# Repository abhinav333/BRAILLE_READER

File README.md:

# Braille e-book reader

Refer work *A. Kulkarni and K. Bhurchandi, "Low Cost E-Book Reading Device for Blind People," 2015 International Conference on Computing Communication Control and Automation, 2015, pp. 516-520, doi: 10.1109/ICCUBEA.2015.106.*

Program, schematics and images<br />
File description:<br />
**braillecode.c** - Lookup table for mapping of aplhanumeric characters to respective braille characters<br />
**buzzer.c** - Contains modules to generate variety of buzzer notifications<br />
**lcd.c** - Consists of lcd display functions. Used only in test mode.<br />
**main.c** - Main program<br />
**mmc.c** - PetitFATFS library: MMC Disk image control modules<br />
**pff.c** - PetitFATFS library: High level SD Card control modules<br />
**pffconf.h** - PetitFATFS library: Version and configuration file<br />
**spi.h** - Low level SPI access functions<br />
**Schematics** - Eagle PCB design files<br />
**test cell** - Contains debug modules for each braille cell<br />
**Hardware** - Device images<br />

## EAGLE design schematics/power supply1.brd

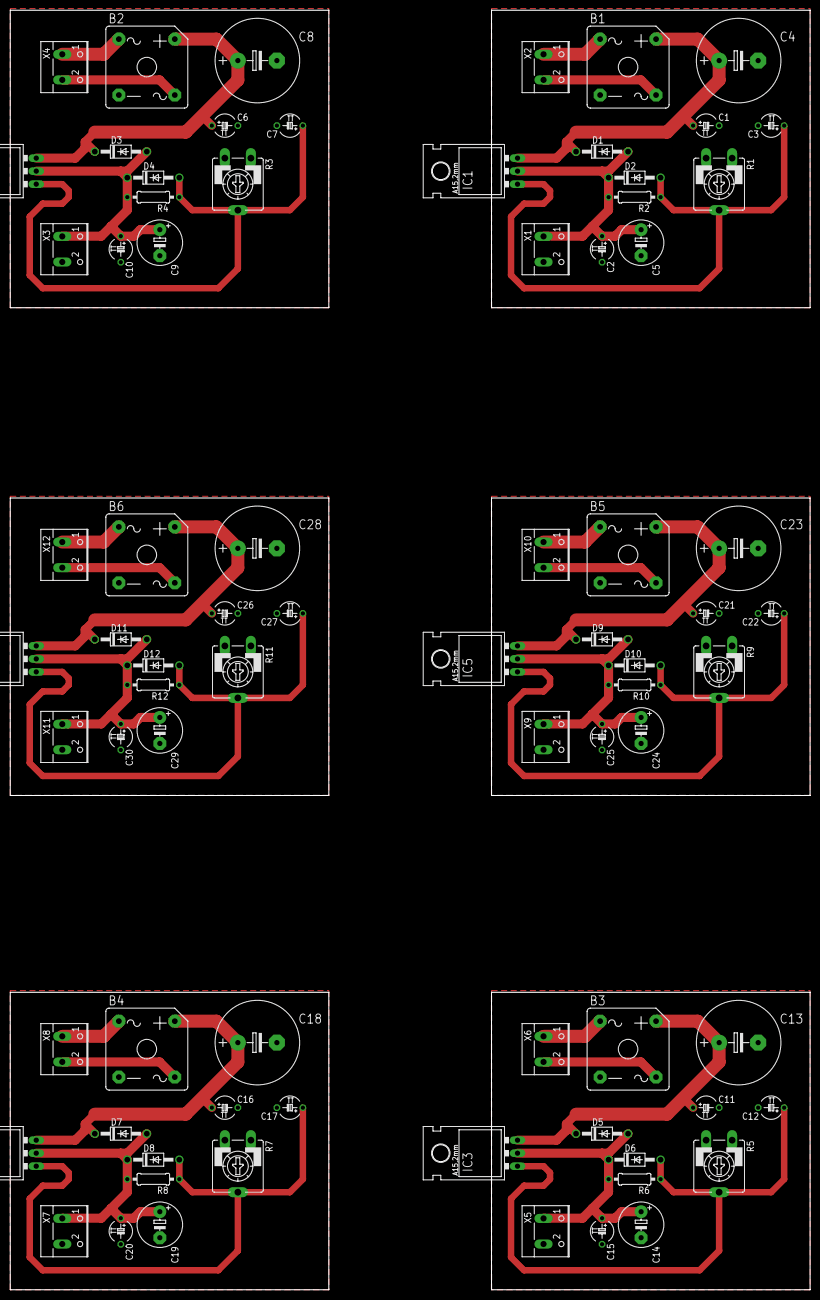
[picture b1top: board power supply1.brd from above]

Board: 2 copper layers, 156.2 x 249.9 mm, 78 parts (0 on the bottom side), 36 nets.

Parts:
B1, B2, B3, B4, B5, B6: GBPC1
C1, C2, C3, C6, C7, C10, C11, C12, C15, C16, C17, C20, C21, C22, C25, C26, C27, C30: 0.1uF; TAP5-45
C4, C8, C13, C18, C23, C28: E7,5-16
C5, C9, C14, C19, C24, C29: E5-8,5
D1, D2, D3, D4, D5, D6, D7, D8, D9, D10, D11, D12: 1N4004; DO41-10
IC1, IC2, IC3, IC4, IC5, IC6: LM317MBT; TO220L1
R1, R3, R5, R7, R9, R11: CA9V
R2, R4, R6, R8, R10, R12: 120R; 0207/10
X1, X2, X3, X4, X5, X6, X7, X8, X9, X10, X11, X12: W237-102

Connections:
AGND: B1.-, C1.-, C2.-, C3.-, C4.-, C5.-, R1.A, X1.2
AGND1: B2.-, C6.-, C7.-, C8.-, C9.-, C10.-, R3.A, X3.2
AGND2: B3.-, C11.-, C12.-, C13.-, C14.-, C15.-, R5.A, X5.2
AGND3: B4.-, C16.-, C17.-, C18.-, C19.-, C20.-, R7.A, X7.2
AGND4: B5.-, C21.-, C22.-, C23.-, C24.-, C25.-, R9.A, X9.2
AGND5: B6.-, C26.-, C27.-, C28.-, C29.-, C30.-, R11.A, X11.2
unnamed: B1.+, C1.+, C4.+, D1.C, IC1.3
unnamed: C2.+, C5.+, D1.A, D2.C, IC1.2, R2.2, X1.1
unnamed: C3.+, D2.A, IC1.1, R1.S, R2.1
unnamed: B2.+, C6.+, C8.+, D3.C, IC2.3
unnamed: C9.+, C10.+, D3.A, D4.C, IC2.2, R4.2, X3.1
unnamed: B1.AC1, X2.1
unnamed: B1.AC2, X2.2
unnamed: C7.+, D4.A, IC2.1, R3.S, R4.1
unnamed: B2.AC1, X4.1
unnamed: B2.AC2, X4.2
unnamed: B3.+, C11.+, C13.+, D5.C, IC3.3
unnamed: C14.+, C15.+, D5.A, D6.C, IC3.2, R6.2, X5.1
unnamed: C12.+, D6.A, IC3.1, R5.S, R6.1
unnamed: B3.AC1, X6.1
unnamed: B3.AC2, X6.2
unnamed: B4.+, C16.+, C18.+, D7.C, IC4.3
unnamed: C19.+, C20.+, D7.A, D8.C, IC4.2, R8.2, X7.1
unnamed: C17.+, D8.A, IC4.1, R7.S, R8.1
unnamed: B4.AC1, X8.1
unnamed: B4.AC2, X8.2
unnamed: B5.+, C21.+, C23.+, D9.C, IC5.3
unnamed: C24.+, C25.+, D9.A, D10.C, IC5.2, R10.2, X9.1
unnamed: C22.+, D10.A, IC5.1, R9.S, R10.1
unnamed: B5.AC1, X10.1
unnamed: B5.AC2, X10.2
unnamed: B6.+, C26.+, C28.+, D11.C, IC6.3
unnamed: C29.+, C30.+, D11.A, D12.C, IC6.2, R12.2, X11.1
unnamed: C27.+, D12.A, IC6.1, R11.S, R12.1
unnamed: B6.AC1, X12.1
unnamed: B6.AC2, X12.2

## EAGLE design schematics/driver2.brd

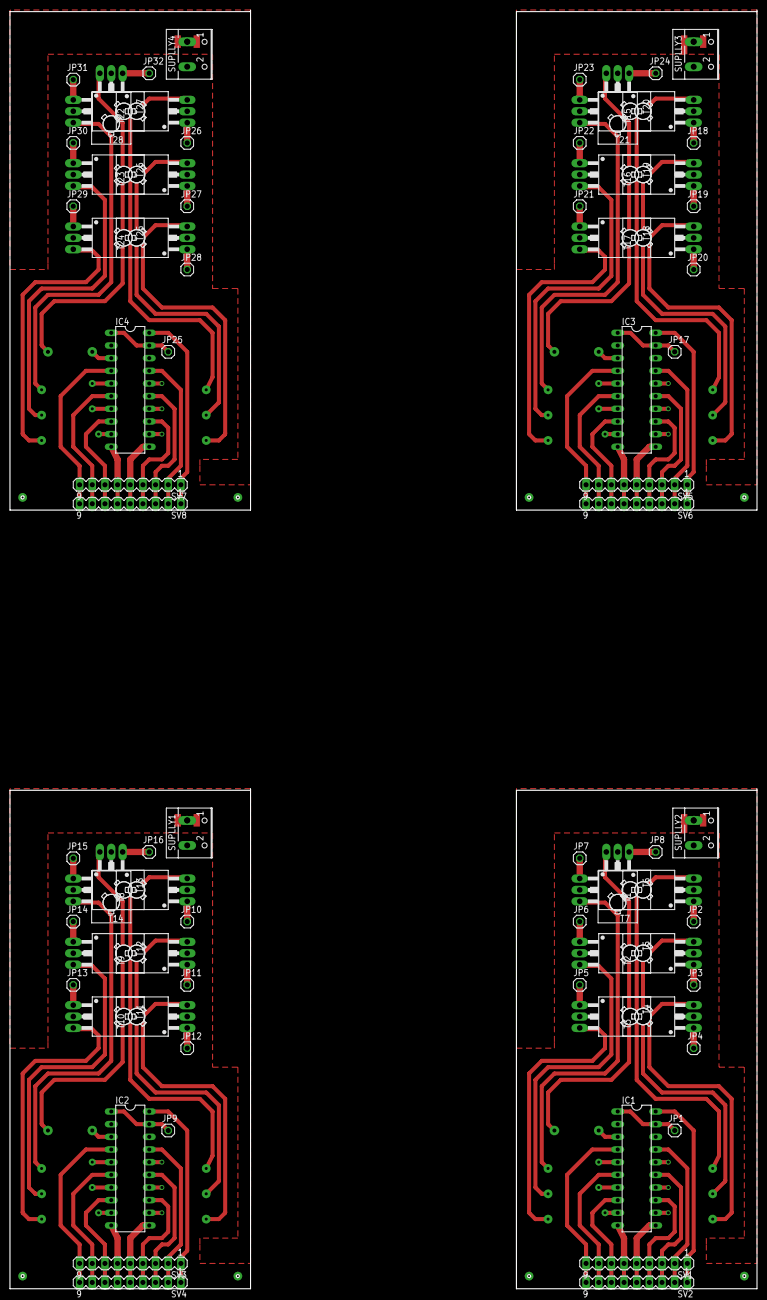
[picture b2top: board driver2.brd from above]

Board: 2 copper layers, 149.9 x 256.5 mm, 76 parts (0 on the bottom side), 96 nets.

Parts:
IC1, IC2, IC3, IC4: 74LS244N; DIL20
JP1, JP2, JP3, JP4, JP5, JP6, JP7, JP8, JP9, JP10, JP11, JP12, JP13, JP14, JP15, JP16, JP17, JP18, JP19, JP20, JP21, JP22, JP23, JP24, JP25, JP26, JP27, JP28, JP29, JP30, JP31, JP32: 1X01
SUPLLY1, SUPLLY2, SUPLLY3, SUPLLY4: W237-102
SV1, SV2, SV3, SV4, SV5, SV6, SV7, SV8: MA09-1
T1, T2, T3, T4, T5, T6, T7, T8, T9, T10, T11, T12, T13, T14, T15, T16, T17, T18, T19, T20, T21, T22, T23, T24, T25, T26, T27, T28: BD139; TO126

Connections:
ACTIVE: IC1.1, IC1.19, JP1.1
ACTIVE1: IC2.1, IC2.19, JP9.1
ACTIVE2: IC3.1, IC3.19, JP17.1
ACTIVE3: IC4.1, IC4.19, JP25.1
GND1: IC1.10, SV1.6, SV2.6
GND4: IC2.10, SV3.6, SV4.6
GND6: IC3.10, SV5.6, SV6.6
GND8: IC4.10, SV7.6, SV8.6
unnamed: IC1.4, SV1.9, SV2.9
unnamed: IC1.6, SV1.8, SV2.8
unnamed: IC1.8, SV1.7, SV2.7
unnamed: IC1.3, T7.3
unnamed: IC1.11, SV1.5, SV2.5
unnamed: IC1.13, SV1.4, SV2.4
unnamed: IC1.16, T1.3
unnamed: JP2.1, T1.1
unnamed: IC1.14, T2.3
unnamed: IC1.12, T3.3
unnamed: IC1.15, SV1.3, SV2.3
unnamed: IC1.9, T4.3
unnamed: IC1.7, T5.3
unnamed: JP3.1, T2.1
unnamed: JP4.1, T3.1
unnamed: JP5.1, T4.1
unnamed: JP6.1, T5.1
unnamed: JP7.1, T6.1
unnamed: JP8.1, T7.1
unnamed: IC1.17, SV1.2, SV2.2
unnamed: IC2.12, T10.3
unnamed: JP10.1, T8.1
unnamed: JP11.1, T9.1
unnamed: JP12.1, T10.1
unnamed: JP13.1, T11.1
unnamed: JP14.1, T12.1
unnamed: JP15.1, T13.1
unnamed: JP16.1, T14.1
unnamed: IC2.3, T14.3
unnamed: IC2.16, T8.3
unnamed: IC2.14, T9.3
unnamed: IC2.9, T11.3
unnamed: IC2.7, T12.3
unnamed: IC2.4, SV3.9, SV4.9
unnamed: IC2.6, SV3.8, SV4.8
unnamed: IC2.8, SV3.7, SV4.7
unnamed: IC2.11, SV3.5, SV4.5
unnamed: IC2.13, SV3.4, SV4.4
unnamed: IC2.15, SV3.3, SV4.3
unnamed: IC2.17, SV3.2, SV4.2
unnamed: IC3.12, T17.3
unnamed: JP18.1, T15.1
unnamed: JP19.1, T16.1
unnamed: JP20.1, T17.1
unnamed: JP21.1, T18.1
unnamed: JP22.1, T19.1
unnamed: JP23.1, T20.1
unnamed: JP24.1, T21.1
unnamed: IC3.3, T21.3
unnamed: IC3.16, T15.3
unnamed: IC3.14, T16.3
unnamed: IC3.9, T18.3
unnamed: IC3.7, T19.3
unnamed: IC3.4, SV5.9, SV6.9
unnamed: IC3.6, SV5.8, SV6.8
unnamed: IC3.8, SV5.7, SV6.7
unnamed: IC3.11, SV5.5, SV6.5
unnamed: IC3.13, SV5.4, SV6.4
unnamed: IC3.15, SV5.3, SV6.3
unnamed: IC3.17, SV5.2, SV6.2
unnamed: IC4.12, T24.3
unnamed: JP26.1, T22.1
unnamed: JP27.1, T23.1
unnamed: JP28.1, T24.1
unnamed: JP29.1, T25.1
unnamed: JP30.1, T26.1
unnamed: JP31.1, T27.1
unnamed: JP32.1, T28.1
unnamed: IC4.3, T28.3
unnamed: IC4.16, T22.3
unnamed: IC4.14, T23.3
unnamed: IC4.9, T25.3
unnamed: IC4.7, T26.3
unnamed: IC4.4, SV7.9, SV8.9
unnamed: IC4.6, SV7.8, SV8.8
unnamed: IC4.8, SV7.7, SV8.7
unnamed: IC4.11, SV7.5, SV8.5
unnamed: IC4.13, SV7.4, SV8.4
unnamed: IC4.15, SV7.3, SV8.3
unnamed: IC4.17, SV7.2, SV8.2
VCC1: IC1.20, SV1.1, SV2.1
VCC2: SUPLLY2.1, T1.2, T2.2, T3.2
VCC3: SUPLLY1.1, T8.2, T9.2, T10.2
VCC4: IC2.20, SV3.1, SV4.1
VCC5: SUPLLY3.1, T15.2, T16.2, T17.2
VCC6: IC3.20, SV5.1, SV6.1
VCC7: SUPLLY4.1, T22.2, T23.2, T24.2
VCC8: IC4.20, SV7.1, SV8.1

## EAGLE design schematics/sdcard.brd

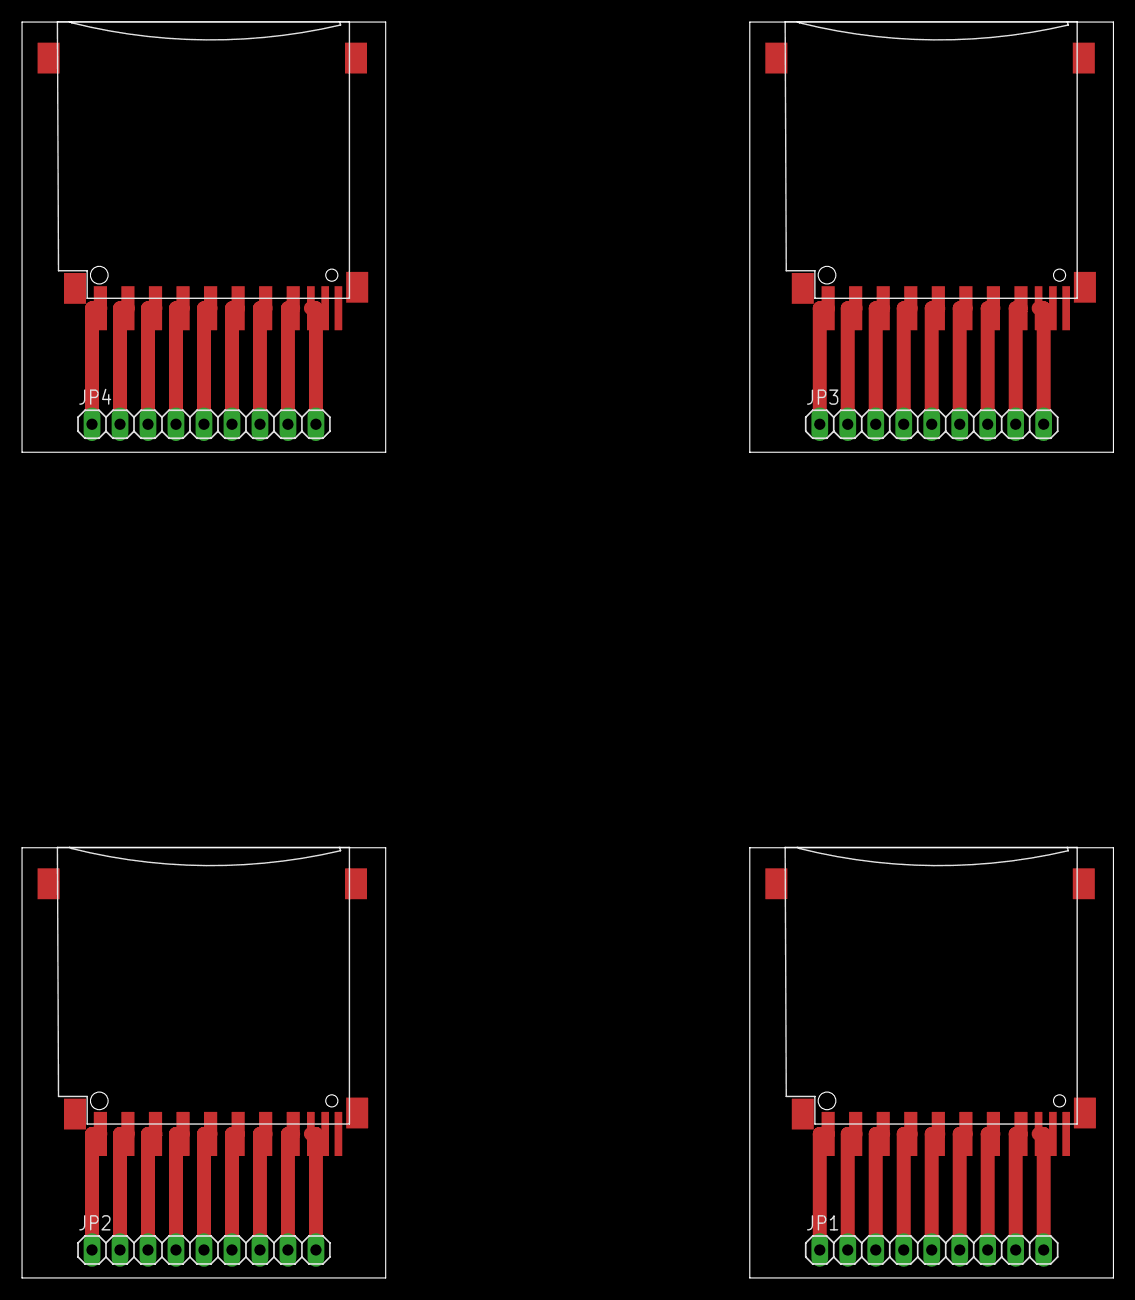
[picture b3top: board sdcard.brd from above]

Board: 2 copper layers, 99.0 x 114.0 mm, 8 parts (0 on the bottom side), 36 nets.

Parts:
JP1, JP2, JP3, JP4: 1X09
U$1, U$2, U$3, U$4: SDMMC06132; 06132

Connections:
unnamed: JP1.2, U$1.1
unnamed: JP1.1, U$1.9
unnamed: JP1.3, U$1.2
unnamed: JP1.6, U$1.5
unnamed: JP1.8, U$1.7
unnamed: JP1.9, U$1.8
unnamed: JP2.2, U$2.1
unnamed: JP2.1, U$2.9
unnamed: JP2.3, U$2.2
unnamed: JP2.6, U$2.5
unnamed: JP2.8, U$2.7
unnamed: JP2.9, U$2.8
unnamed: JP3.2, U$3.1
unnamed: JP3.1, U$3.9
unnamed: JP3.3, U$3.2
unnamed: JP3.6, U$3.5
unnamed: JP3.8, U$3.7
unnamed: JP3.9, U$3.8
unnamed: JP4.2, U$4.1
unnamed: JP4.1, U$4.9
unnamed: JP4.3, U$4.2
unnamed: JP4.6, U$4.5
unnamed: JP4.8, U$4.7
unnamed: JP4.9, U$4.8
VDD: JP1.5, U$1.4
VDD1: JP2.5, U$2.4
VDD2: JP3.5, U$3.4
VDD3: JP4.5, U$4.4
VSS1: JP1.4, U$1.3
VSS2: JP1.7, U$1.6
VSS3: JP2.4, U$2.3
VSS4: JP2.7, U$2.6
VSS5: JP3.4, U$3.3
VSS6: JP3.7, U$3.6
VSS7: JP4.4, U$4.3
VSS8: JP4.7, U$4.6

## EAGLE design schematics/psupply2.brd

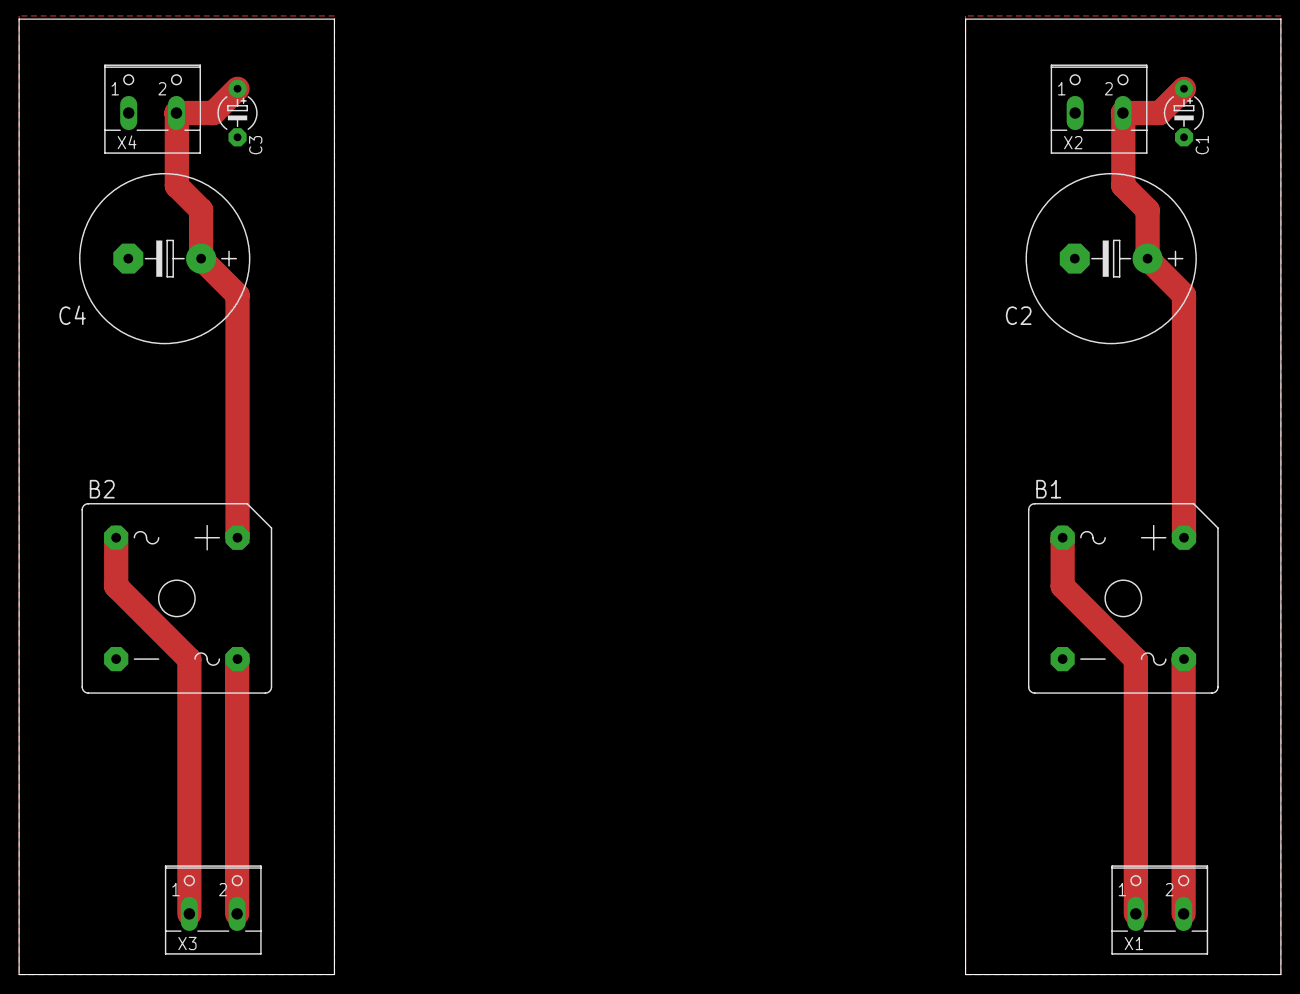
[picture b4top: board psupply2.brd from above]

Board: 2 copper layers, 132.1 x 100.0 mm, 10 parts (0 on the bottom side), 8 nets.

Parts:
B1, B2: GBPC80X
C1, C3: E5-4
C2, C4: E7,5-18
X1, X2, X3, X4: W237-102

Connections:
GND: B1.-, C1.-, C2.-, X2.1
GND1: B2.-, C3.-, C4.-, X4.1
unnamed: B1.AC1, X1.1
unnamed: B1.AC2, X1.2
unnamed: B1.+, C1.+, C2.+, X2.2
unnamed: B2.AC1, X3.1
unnamed: B2.AC2, X3.2
unnamed: B2.+, C3.+, C4.+, X4.2

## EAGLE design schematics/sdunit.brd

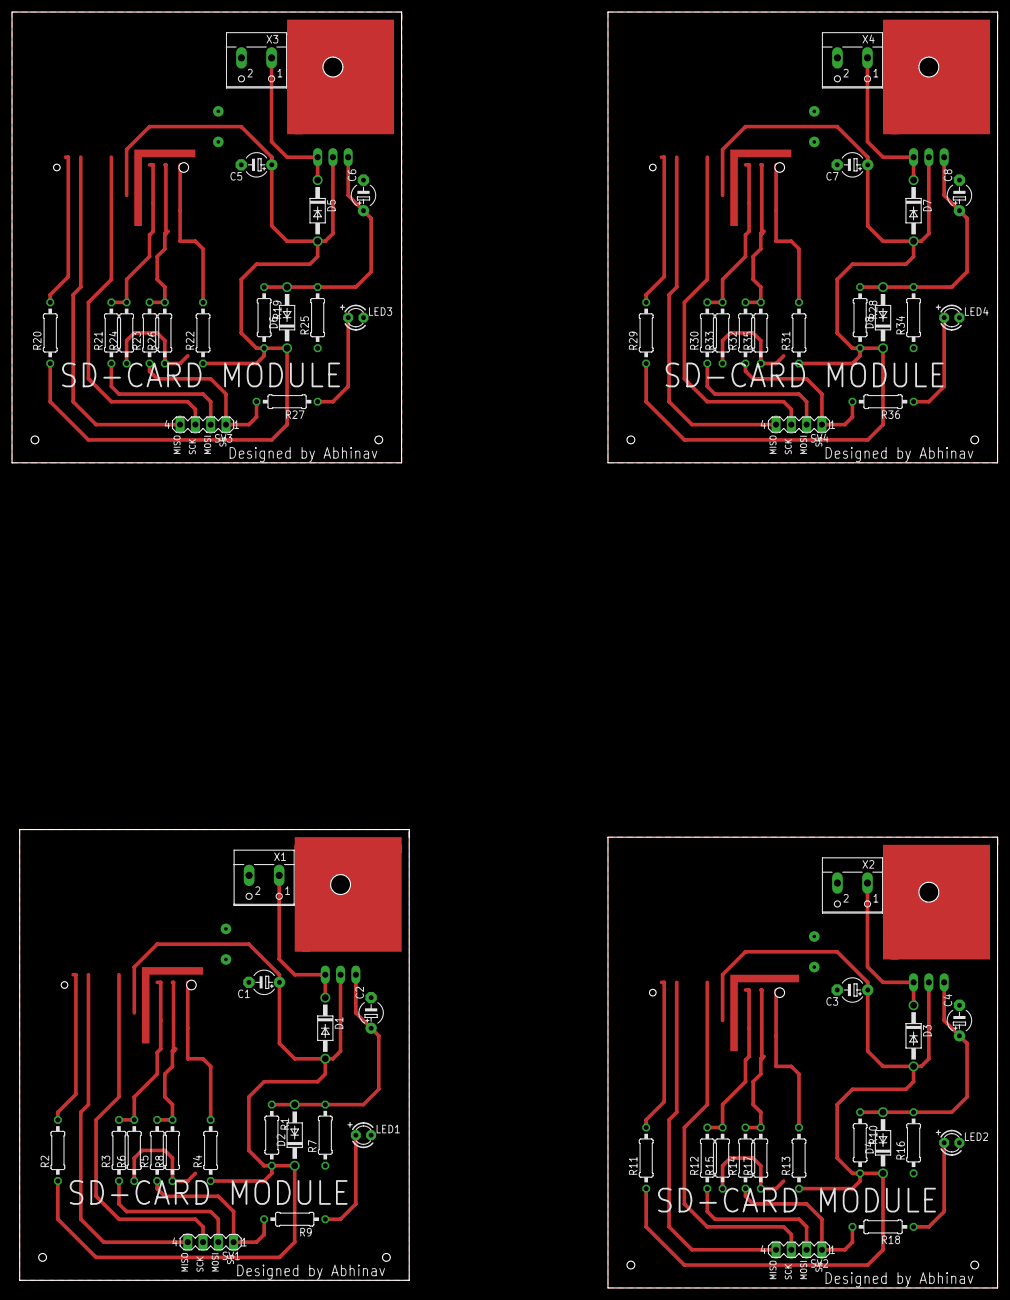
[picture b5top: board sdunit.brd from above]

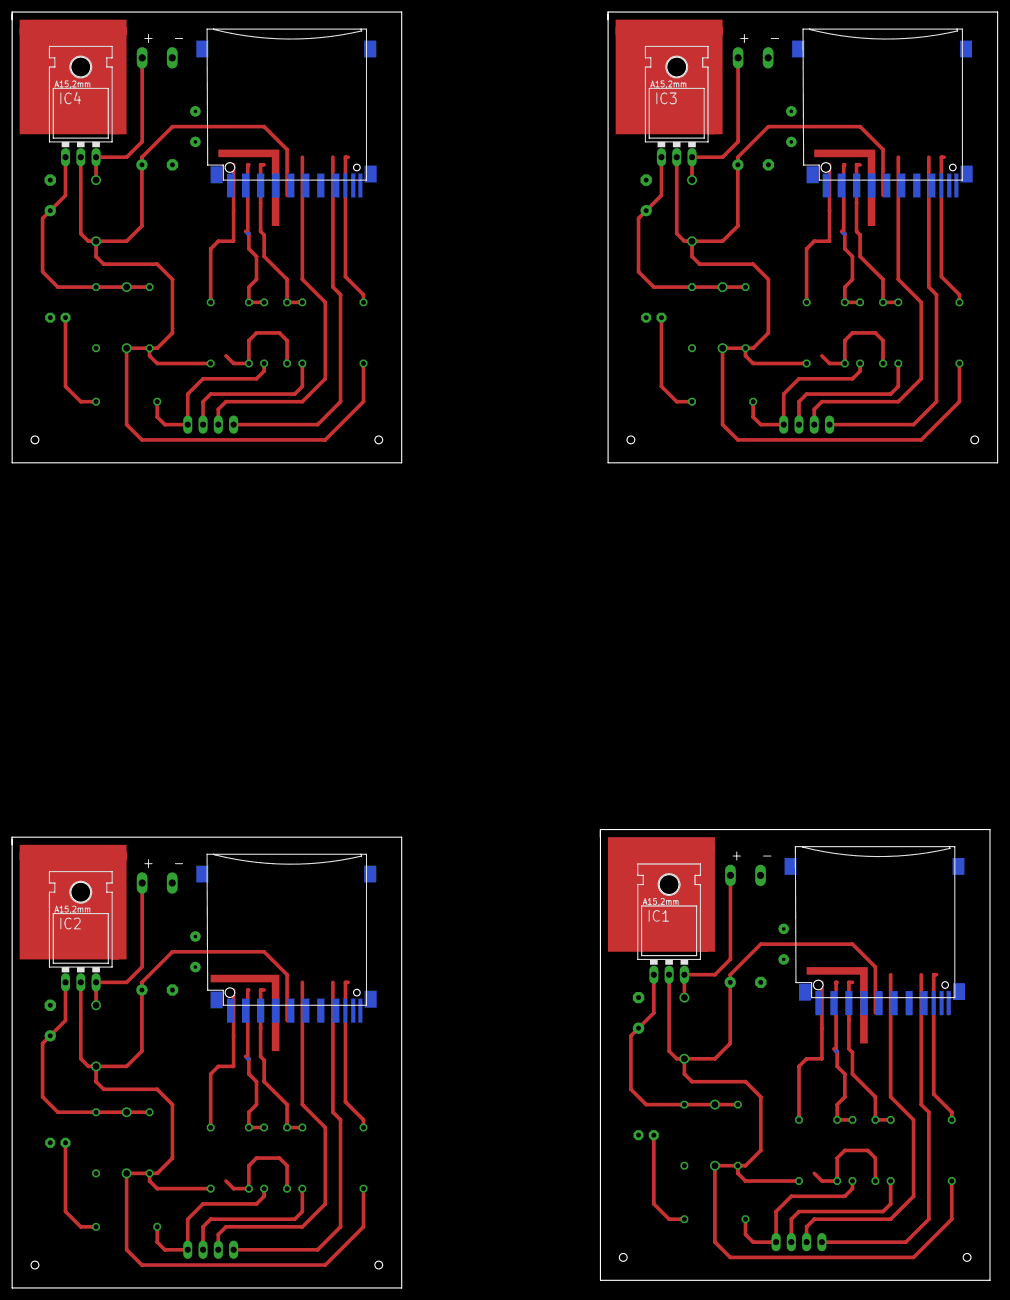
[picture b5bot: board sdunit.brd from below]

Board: 2 copper layers, 163.8 x 212.1 mm, 72 parts (8 on the bottom side), 56 nets.

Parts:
C1, C2, C3, C4, C5, C6, C7, C8: 0.1uf; E5-4
D1, D2, D3, D4, D5, D6, D7, D8: 1N4004; DO41-10
IC1, IC2, IC3, IC4: LM317MABT; TO220L1
LED1, LED2, LED3, LED4: LED3MM
R1, R9, R10, R18, R19, R27, R28, R36: 220E; 0207/10
R2, R4, R6, R8, R11, R13, R15, R17, R20, R22, R24, R26, R29, R31, R33, R35: 47k; 0207/10
R3, R5, R12, R14, R21, R23, R30, R32: 22k; 0207/10
R7, R16, R25, R34: 360E; 0207/10
SV1, SV2, SV3, SV4: MA04-1
U$1, U$2, U$3, U$4: SDMMC06132; 06132
X1, X2, X3, X4: W237-102

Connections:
GND1: C1.-, C2.-, LED1.K, R6.1, R7.1, R8.1, X1.2
GND2: C3.-, C4.-, LED2.K, R15.1, R16.1, R17.1, X2.2
GND3: C5.-, C6.-, LED3.K, R24.1, R25.1, R26.1, X3.2
GND4: C7.-, C8.-, LED4.K, R33.1, R34.1, R35.1, X4.2
unnamed: D1.C, IC1.3, X1.1
unnamed: C2.+, D2.A, IC1.1, R1.1, R7.2
unnamed: R3.2, R6.2, U$1.2
unnamed: R5.1, R9.2, SV1.1
unnamed: R5.2, R8.2, U$1.1
unnamed: SV1.4, U$1.7
unnamed: R2.2, U$1.8
unnamed: R4.2, U$1.9
unnamed: R3.1, SV1.2
unnamed: SV1.3, U$1.5
unnamed: D3.C, IC2.3, X2.1
unnamed: C4.+, D4.A, IC2.1, R10.1, R16.2
unnamed: R12.2, R15.2, U$2.2
unnamed: R14.1, R18.2, SV2.1
unnamed: R14.2, R17.2, U$2.1
unnamed: SV2.4, U$2.7
unnamed: R11.2, U$2.8
unnamed: R13.2, U$2.9
unnamed: R12.1, SV2.2
unnamed: SV2.3, U$2.5
unnamed: D5.C, IC3.3, X3.1
unnamed: C6.+, D6.A, IC3.1, R19.1, R25.2
unnamed: R21.2, R24.2, U$3.2
unnamed: R23.1, R27.2, SV3.1
unnamed: R23.2, R26.2, U$3.1
unnamed: SV3.4, U$3.7
unnamed: R20.2, U$3.8
unnamed: R22.2, U$3.9
unnamed: R21.1, SV3.2
unnamed: SV3.3, U$3.5
unnamed: D7.C, IC4.3, X4.1
unnamed: C8.+, D8.A, IC4.1, R28.1, R34.2
unnamed: R30.2, R33.2, U$4.2
unnamed: R32.1, R36.2, SV4.1
unnamed: R32.2, R35.2, U$4.1
unnamed: SV4.4, U$4.7
unnamed: R29.2, U$4.8
unnamed: R31.2, U$4.9
unnamed: R30.1, SV4.2
unnamed: SV4.3, U$4.5
S$1: LED2.A, R18.1
S$2: LED1.A, R9.1
S$3: LED3.A, R27.1
S$4: LED4.A, R36.1
VCC1: C1.+, D1.A, D2.C, IC1.2, R1.2, R2.1, R4.1, U$1.4
VCC2: C3.+, D3.A, D4.C, IC2.2, R10.2, R11.1, R13.1, U$2.4
VCC3: C5.+, D5.A, D6.C, IC3.2, R19.2, R20.1, R22.1, U$3.4
VCC4: C7.+, D7.A, D8.C, IC4.2, R28.2, R29.1, R31.1, U$4.4
VSS1: U$1.3, U$1.6
VSS2: U$2.3, U$2.6
VSS3: U$3.3, U$3.6
VSS4: U$4.3, U$4.6

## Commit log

2015-12-16 Essentials
2016-02-14 File descriptions
